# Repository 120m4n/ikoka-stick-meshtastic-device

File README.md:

# Ikoka Stick Meshtastic Device

## Ikoka! (行こか!)

“行こか?” or “行こか!” is [Kansai dialect](https://en.wikipedia.org/wiki/Kansai_dialect) for “shall we go?” or “let’s go!”.

I hope that building these long-range Meshtastic designs inspires you to go on your next [DXing](https://en.wikipedia.org/wiki/DXing) adventure.

## Features

- LoRa
  - Up to 33 dBm (2 W) output power
  - 410–493 MHz (433 MHz band) or 850–930 MHz (868/915/923 MHz band)
- Bluetooth 5 LE
- Wi-Fi 4 (2.4 GHz)
- USB 5V powered, optional LiPo battery with charging
- 0.96" OLED display

Feature set above depends on part selection.

### Hardware

### Parts Selection

Several options are available depending on the feature set you need.

#### Microcontroller

- [Seeed Studio XIAO-nRF52840](https://www.seeedstudio.com/Seeed-XIAO-BLE-nRF52840-p-5201.html) - Bluetooth 5/LE
- [Seeed Studio XIAO-ESP32-S3](https://www.seeedstudio.com/XIAO-ESP32S3-p-5627.html) - Bluetooth 5/LE and Wi-Fi 4 (2.4 GHz)

#### LoRa Module (v3: E22P)

Version 3 uses the EBYTE E22P (e.g. E22P-915M30S) instead of the E22, ported from [tahnok's fork](https://github.com/tahnok/ikoka-stick-meshtastic-device) (commit 366648b). Same footprint, pin compatible except for 2 pins:

- Pin 6 is `RXEN` on the E22 (driven by XIAO D5 (pin 6) / `SX126X_RXEN` in firmware). On the E22P it is `EN` and must be high to transmit or receive. It now goes to the common pad of solder jumper JP1 (under the XIAO): pads 1–2 are bridged by default and tie `EN` to 3.3V. To drive it from XIAO D5 (pin 6) instead, cut the 1–2 trace and bridge pads 2–3.
- Pin 7 is `TXEN` on the E22 and `T/R CTRL` on the E22P (high = TX, low = RX). It stays connected to the radio's `DIO2`, which drives it correctly.

The original E22 still works with JP1 bridged 2–3 (RXEN on D5).

##### JP1 configuration

| Module | JP1 | Firmware |
|---|---|---|
| E22P | 1–2 (factory default) | Stock Meshtastic/MeshCore |
| E22 | 2–3 (cut 1–2, bridge 2–3) | Stock Meshtastic/MeshCore |
| E22P with software power-down | 2–3 | Firmware that treats D5 as an enable (held high in TX and RX) |

Never bridge all three pads: that shorts 3.3V to D5. JP1 sits under the XIAO, so pull the XIAO from its sockets to change it.

U2 in the BOM is the [E22P-915M30S](https://www.cdebyte.com/products/E22P-915M30S) (902–928 MHz at 30 dBm), JLCPCB/LCSC part [C51912672](https://jlcpcb.com/partdetail/54616328-E22P915M30S/C51912672) (extended part). For the 868 MHz band use the E22P-868M30S. The E22 modules below also fit (set JP1 to 2–3); the E22-900M30S is LCSC C411294.

- [E22-400M22S](https://www.cdebyte.com/products/E22-400M22S) (410–493 MHz at 22 dBm)
- [E22-400M30S](https://www.cdebyte.com/products/E22-400M30S) (410–493 MHz at 30 dBm)
- [E22-400M33S](https://www.cdebyte.com/products/E22-400M33S) (410–493 MHz at 33 dBm)
- [E22-900M22S](https://www.cdebyte.com/products/E22-900M22S) (850–930 MHz at 22 dBm)
- [E22-900M30S](https://www.cdebyte.com/products/E22-900M30S) (850–930 MHz at 30 dBm)
- [E22-900M33S](https://www.cdebyte.com/products/E22-900M33S) (850–930 MHz at 33 dBm)

#### Power (v2)

Version 2 drops the on-board 21700 battery holder. The board runs entirely from the XIAO's USB 5V (VBUS): D3 (SS34) feeds the boost input and blocks backfeed into VBUS, and the Q1 (AO3401A) battery/USB power path is kept for an optional LiPo on the PicoBlade connectors.

The LoRa supply (+5V2_LORA) comes from an XL3608 boost module (24.4 × 13.7 mm) mounted flat on the back side, footprint `Booster_Module:Booster_XL3608_24.4x13.7mm_SMD`:

- SMD pads only, no holes, so nothing pokes through to the front side. It sits between the XIAO and the E22, not behind the E22's RF area.
- The only exposed copper under the module is its own 4 pads; vias are tented. Put Kapton tape or double-sided foam tape between the module and the board.
- Pad positions are assumed (1.5 mm from each corner, VIN/VOUT on one long side and GND on the other, labelled on the silkscreen). Check them against your module with a caliper before ordering.

#### Lithium-polymer Battery (4.2V charging termination, optional)

- Lithium-polymer pouch battery cell (4.2V charge termination; connector: Molex PicoBlade 1x02P, pitch 1.25mm)

##### Wiring for Battery Charging

You will need a PicoBlade Female-to-Pigtail cable assembly such as Molex [218112-0200](https://www.molex.com/en-us/products/part-detail/2181120200). A compatible cable ships with Heltec Wireless and LILYGO LoRa products so you probably have spares you can use. [Muzi Works](https://muzi.works/products/battery-cable-molex-picoblade) and [Rokland](https://store.rokland.com/products/battery-connector-cables-battery-wires-jst-1-25-5pcs-for-lilygo-and-heltec) also sell compatible cables.

1. Trim the pigtail length to around 5cm if it is longer
2. Strip 2mm of insulation from each pigtail, then twist and tin the wire strands
3. Solder the red pigtail (or pin 1) to the BAT+ pad on the back of the XIAO module
4. Solder the black pigtail (or pin 2) to the BAT- pad on the back of the XIAO module
5. Plug the cable into the XIAO Charger connector on the Ikoka Stick

In my previous design, the [Ikoka Nano](https://github.com/ndoo/ikoka-nano-meshtastic-device), the XIAO module was SMD soldered onto the board, while the BAT+ pad was soldered through a plated through-hole via. However, the actual solder joint is buried and couldn't be inspected for continuity, quality and ensuring the BAT+ pad was not shorted to the BAT- pad.

In the interest of ease-of-assembly and keeping the XIAO module interchangeable, while not wasting the built-in battery charging circuit on XIAO modules, this approach was chosen instead.

#### OLED Display (Optional)

- Generic SSD1306 0.96" OLED display modules with 2.54mm pin headers [https://www.aliexpress.com/item/1005008077705181.html]((AliExpress))
- v3 header J6 pinout is `GND, VCC (3.3V), SCL, SDA` (pin 1 to 4), marked `-`/`+` on the silkscreen, matching the common GND-first modules (ported from tahnok's fork). v1/v2 had `VCC, GND, SCL, SDA`. Check your module's pin order before soldering.

## Firmware

### GPIO Assignment

| XIAO Pin | Function | XIAO-nRF52840 | XIAO-ESP32-S3 |
|---|---|---|---|
| 1 (D0) | User button | 2 (P0.02) | 1 |
| 2 (D1) | EBYTE E22 - DIO1 | 3 (P0.03) | 2 |
| 3 (D2) | EBYTE E22 - RST | 28 (P0.28) | 3 |
| 4 (D3) | EBYTE E22 - BUSY | 29 (P0.29) | 4 |
| 5 (D4) | EBYTE E22 - SPI NSS | 4 (P0.04) | 5 |
| 6 (D5) | EBYTE E22 - RXEN | 5 (P0.05) | 6 |
| 7 (D6) | SSD1306 OLED - I2C SDA | 43 (P1.11) | 43 |
| 8 (D7) | SSD1306 OLED - I2C SCL | 44 (P1.12) | 44 |
| 9 (D8) | EBYTE E22 - SPI SCK | 45 (P1.13) | 7 |
| 10 (D9) | EBYTE E22 - SPI MISO | 46 (P1.14) | 8 |
| 11 (D10) | EBYTE E22 - SPI MOSI | 47 (P1.15) | 9 |
| 12 | SSD1306 OLED - 3.3V | 3V3 | 3V3 |
| 13 | GND | GND | GND |
| 14 | NC | 5V | 5V |

### Meshtastic Compatibility

The XIAO module is intended to be socketed with pin headers/pin sockets, to allow swapping out modules depending on what features are needed (Bluetooth, Wi-Fi, different power consumption profiles, etc.); Compatibility with official Meshtastic firmware depends on the inserted XIAO board.

#### XIAO-nRF52840

- EBYTE E22 LoRa
  - LoRa pins are identical to the officially-supported [Seeed Xiao NRF52840 Kit](https://www.seeedstudio.com/XIAO-nRF52840-Wio-SX1262-Kit-for-Meshtastic-p-6400.html) on [Meshtastic Web Flasher](https://flasher.meshtastic.org/)
  - LoRa will work out of the box on officially-supported firmware
  - Special consideration must be taken if using the E22-900M33S module
    - Set the transmit power to ≤ 9 dBm on first use (when setting the LoRa region)
    - **Transmit power must never be set greater than 9 dBm*- to avoid damaging the module's RF frontend
- SSD1306 OLED I2C
  - Pin D6/P1.11 and D7/P1.12 are [reserved for the L76K GPS module in the officially-supported variant](https://github.com/meshtastic/firmware/blob/152b8b1b0235bc461c6e4451fbcdac0987b8bf90/variants/seeed_xiao_nrf52840_kit/variant.h#L137-L138)
  - A custom firmware must be built to define these pins as I2C (TODO)
- User button
  - Pin D0/P0.02 is [reserved for the L76K GPS module in the officially supported variant](https://github.com/meshtastic/firmware/blob/152b8b1b0235bc461c6e4451fbcdac0987b8bf90/variants/seeed_xiao_nrf52840_kit/variant.h#L144)
  - A custom firmware must be built to define this pin as the user button (TODO)

### XIAO-ESP32-S3

- Pin definitions are different from the officially-supported [Seeed Xiao ESP32-S3 Kit](https://www.seeedstudio.com/Wio-SX1262-with-XIAO-ESP32S3-p-5982.html)
  - This is because Seeed uses GPIOs on the 30-pin board-to-board press-fit connector instead of the standard XIAO pins
  - A custom firmware must be built (TODO)

## PCB Renders

### PCB Top

### PCB Bottom

### Rotating GIF

(Rendered with [kicad-render](https://github.com/linalinn/kicad-render).)

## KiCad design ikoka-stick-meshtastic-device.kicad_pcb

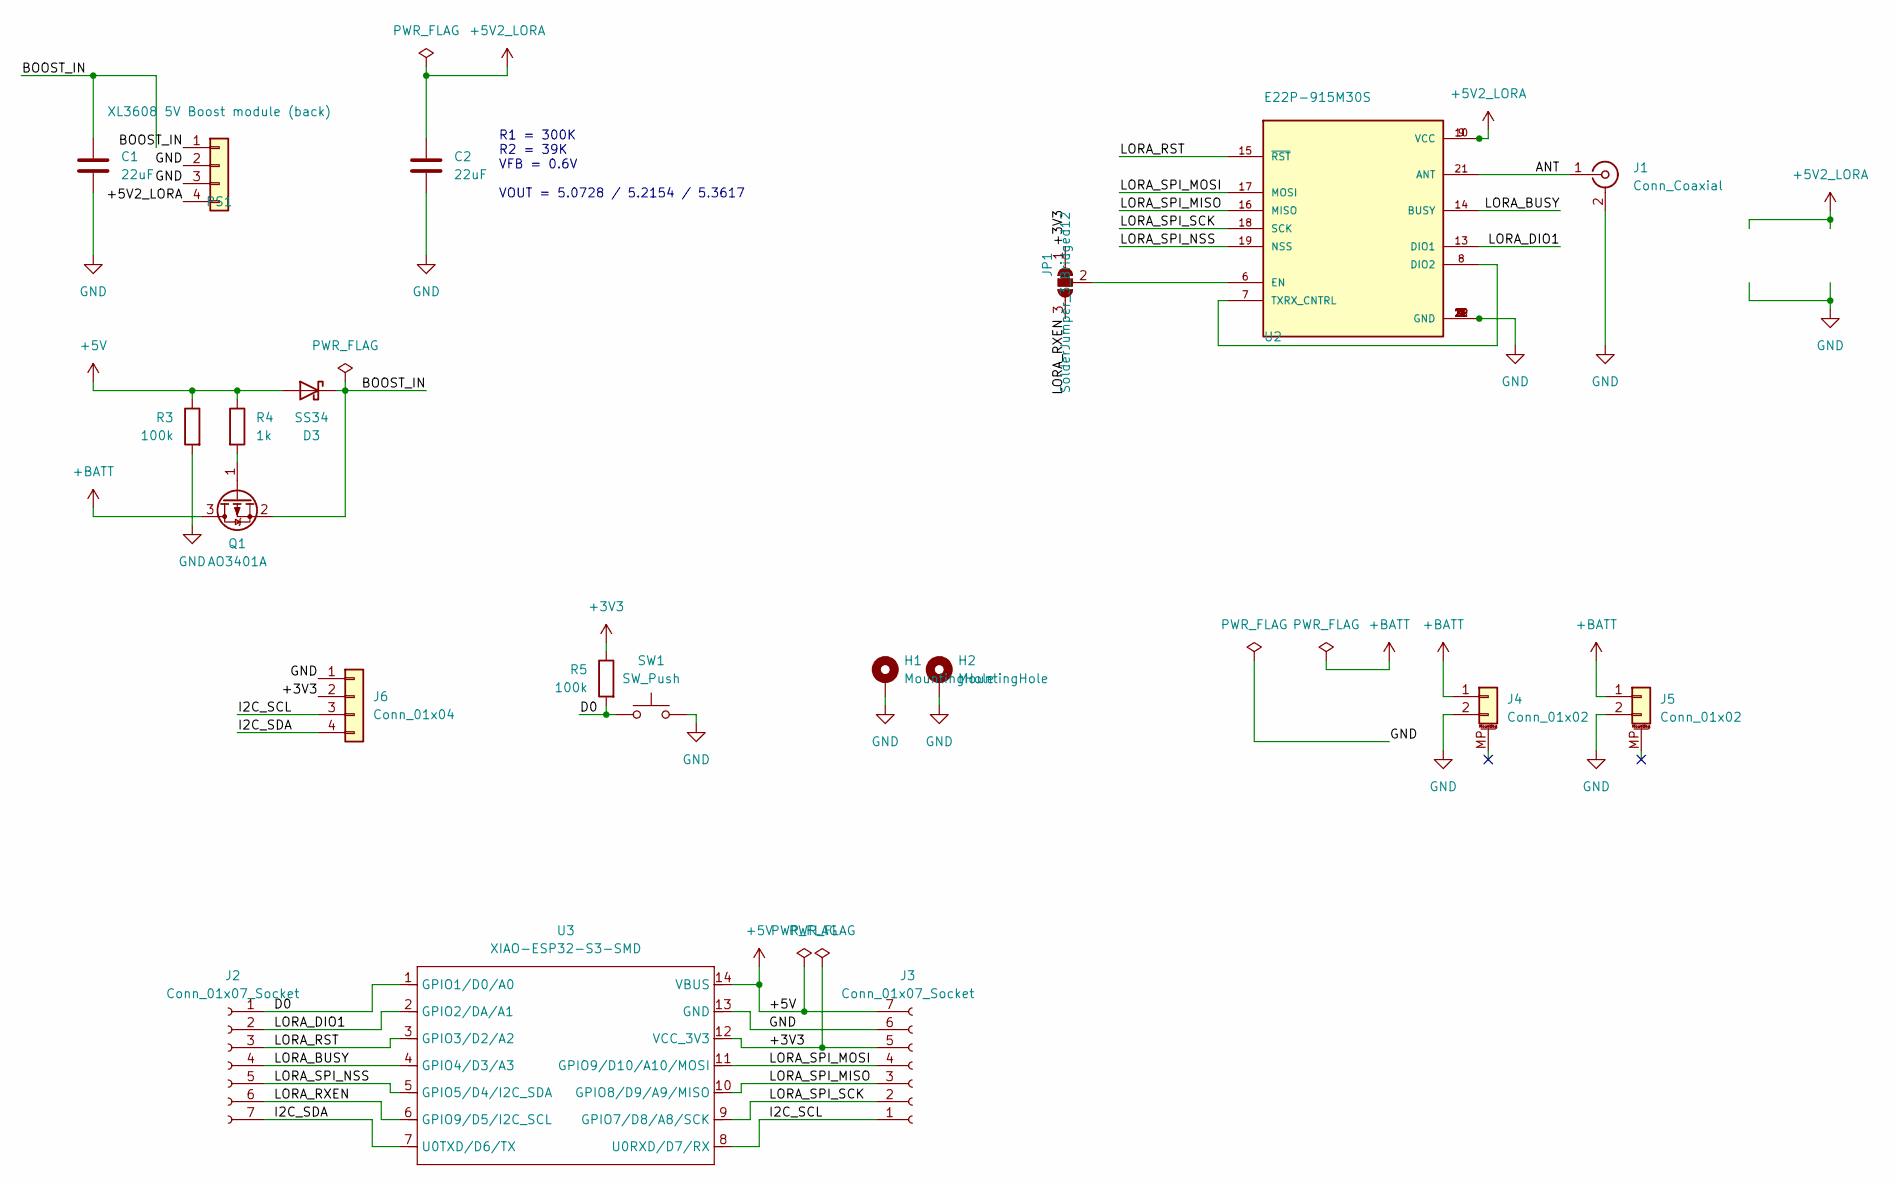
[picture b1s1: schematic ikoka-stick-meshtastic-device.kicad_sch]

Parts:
C1, C2: 22uF; C_0603_1608Metric; LCSC C59461
D3: SS34; D_SMA; LCSC C8678
H1, H2: MountingHole; MountingHole_2.2mm_M2_Pad_Via
J1: Conn_Coaxial; SMA_Samtec_SMA-J-P-H-ST-EM1_EdgeMount; LCSC C5250058
J2, J3: Conn_01x07_Socket; PinSocket_1x07_P2.54mm_Vertical_SMD_Pin1Left; LCSC C42379199
J4, J5: Conn_01x02; Molex_PicoBlade_53261-0271_1x02-1MP_P1.25mm_Horizontal; LCSC C2905009
J6: Conn_01x04; PinSocket_1x04_P2.54mm_Vertical_SMD_Pin1Right; LCSC C46635840
JP1: SolderJumper_3_Bridged12; SolderJumper-3_P1.3mm_Bridged12_RoundedPad1.0x1.5mm_NumberL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
PS1: XL3608 5V Boost module (back); Booster_XL3608_24.4x13.7mm_SMD
Q1: AO3401A; SOT-23; LCSC C15127
R3, R5: 100k; R_0603_1608Metric; LCSC C25803
R4: 1k; R_0603_1608Metric; LCSC C21190
SW1: SW_Push; SW_Push_1P1T_XKB_TS-1187A; LCSC C318884
U2: E22P-915M30S; XCVR_E22-900M30S; PARTREV 1.2; LCSC C51912672
U3: XIAO-ESP32-S3-SMD; XIAO-ESP32S3-DIP; LCSC C9900124959

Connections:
+3V3: J3.5, J6.2, JP1.1 (A), R5.1, U3.12 (VCC_3V3)
+5V: D3.2 (A), J3.7, R3.1, R4.1, U3.14 (VBUS)
+5V2_LORA: C2.1, PS1.4, U2.9 (VCC), U2.10 (VCC)
+BATT: J4.1, J5.1, Q1.3 (D)
/ANT: J1.1 (In), U2.21 (ANT)
/BOOST_IN: C1.1, D3.1 (K), PS1.1, Q1.2 (S)
/D0: J2.1, R5.2, SW1.1, U3.1 (GPIO1/D0/A0)
/I2C_SCL: J3.1, J6.3, U3.8 (U0RXD/D7/RX)
/I2C_SDA: J2.7, J6.4, U3.7 (U0TXD/D6/TX)
/LORA_BUSY: J2.4, U2.14 (BUSY), U3.4 (GPIO4/D3/A3)
/LORA_DIO1: J2.2, U2.13 (DIO1), U3.2 (GPIO2/DA/A1)
/LORA_RST: J2.3, U2.15 (~RST), U3.3 (GPIO3/D2/A2)
/LORA_RXEN: J2.6, JP1.3 (B), U3.6 (GPIO9/D5/I2C_SCL)
/LORA_SPI_MISO: J3.3, U2.16 (MISO), U3.10 (GPIO8/D9/A9/MISO)
/LORA_SPI_MOSI: J3.4, U2.17 (MOSI), U3.11 (GPIO9/D10/A10/MOSI)
/LORA_SPI_NSS: J2.5, U2.19 (NSS), U3.5 (GPIO5/D4/I2C_SDA)
/LORA_SPI_SCK: J3.2, U2.18 (SCK), U3.9 (GPIO7/D8/A8/SCK)
GND: C1.2, C2.2, H1.1 (1_1), H2.1 (1_1), J1.2 (Ext), J3.6, J4.2, J5.2, J6.1, PS1.2, PS1.3, R3.2, SW1.2, U2.1 (GND), U2.2 (GND), U2.3 (GND), U2.4 (GND), U2.5 (GND), U2.11 (GND), U2.12 (GND), U2.20 (GND), U2.22 (GND), U3.13 (GND)
unnamed: JP1.2 (C), U2.6 (RXEN)
unnamed: Q1.1 (G), R4.2
unnamed: U2.7 (TXEN), U2.8 (DIO2)

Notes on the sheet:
R1 = 300K R2 = 39K VFB = 0.6V VOUT = 5.0728 / 5.2154 / 5.3617

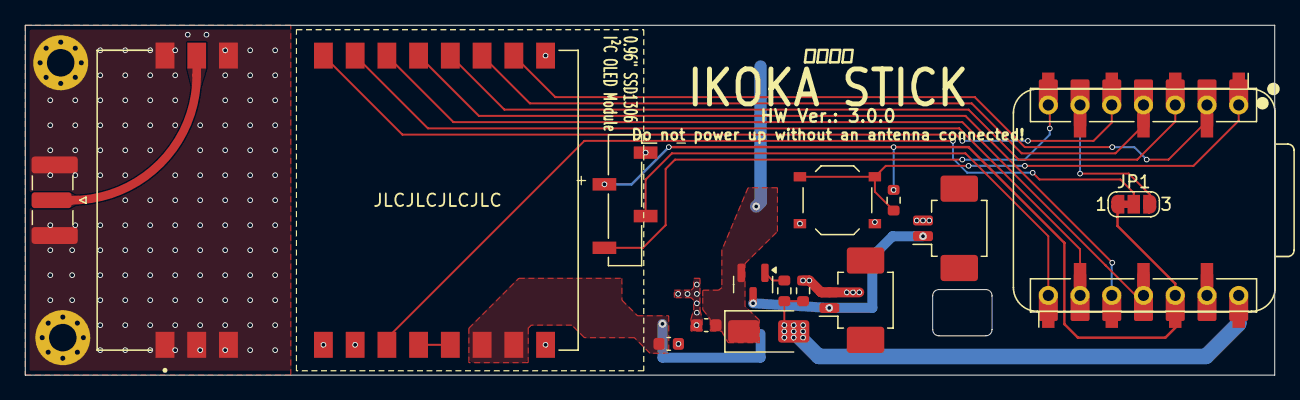
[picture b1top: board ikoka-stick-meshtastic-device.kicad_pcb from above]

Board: 2 copper layers, 100.0 x 28.0 mm, 20 parts (1 on the bottom side), 21 nets.
